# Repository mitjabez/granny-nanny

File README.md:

# About

IoT light sensor app. Light state is sent to a rest endpoint which saves it to Google Cloud
Monitoring.

I use this to monitor the light at my mom's house so I know if she's ok.

The app consists of 2 parts located in `src/`:
- esp8266_monitor. This is the sender built on ESP8266.
- http_iot_streamer. HTTP REST web service storing the data in Google Cloud Monitoring.

# esp8266_monitor

## Prerequisites:

- Copy `config.h.example` to `config.h` and edit all values marked with `CHANGEME`.
- https://github.com/plerup/makeEspArduino

## Build

    make

    make flash

# Hardware

Eagle PCB and schematic files (plus exported PDFs) are in `hardware/`:
- `hardware/granny-nanny.sch` / `hardware/granny-nanny-schematic.pdf` — Schematic
- `hardware/granny-nanny.brd` / `hardware/granny-nanny-board.pdf` — PCB layout

## Known issue: must be powered on in the light

The photocell voltage divider (`R1` + `VR2`) is wired to `GPIO2` on the ESP-01. Because `GPIO2` is a boot-strapping pin that must be `HIGH` at startup, powering on or rebooting the device in the dark (or with the photocell disconnected) allows `VR2` to pull `GPIO2` `LOW`, causing the ESP-01 to hang on boot with both the red and blue LEDs constantly lit.

Make sure there is enough light on the sensor when turning the device on. Once booted, darkness is handled normally.

# http_iot_streamer

## Prerequisites

- Service account named `svc-http-iot-streamer`.
- Copy `.env.yaml.example` to `.env.yaml` and edit the corresponding values. File is located in
`src/http_iot_streamer/`.

## Deploy

    ./scripts/deploy.sh

## Run locally

Create a virtual environment and install the service dependencies:

    cd src/http_iot_streamer
    python3 -m venv .venv
    source .venv/bin/activate
    python -m pip install -r requirements.txt

Set the required configuration values, then start the service:

    export API_KEY=local-api-key
    export ENVIRONMENT=local
    export PROJECT=your-gcp-project-id
    python main.py

The service listens on `http://localhost:8080`. To send it a test request:

    curl --data '{"light": true}' --header 'content-type: application/json' \
      'http://localhost:8080/light/status?apikey=local-api-key'

Valid requests write a metric to Google Cloud Monitoring, so local runs need Google
Cloud credentials that can write metrics to the selected project.

## Test

This will send a test payload to the deployed service:

    ./scripts/test.sh

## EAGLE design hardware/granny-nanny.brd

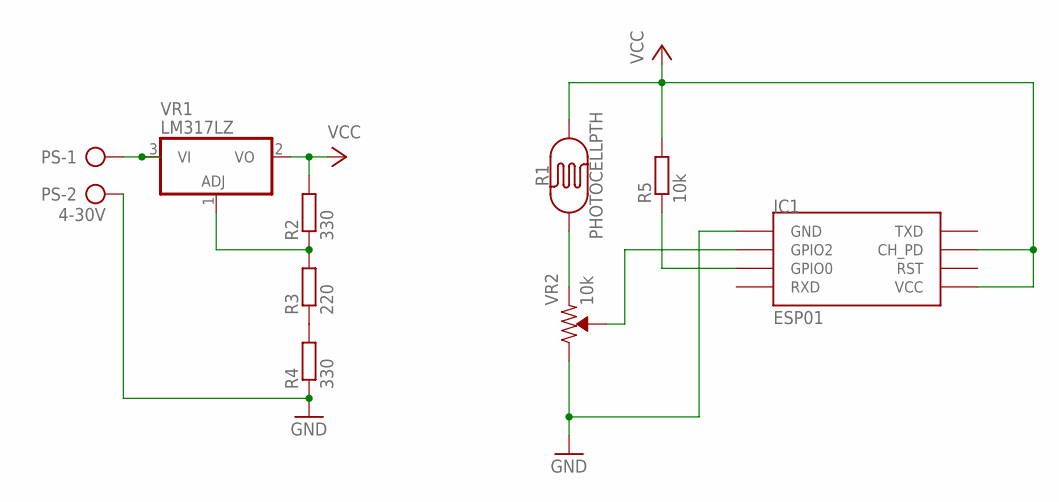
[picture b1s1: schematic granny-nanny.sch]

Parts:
IC1: ESP01
PS: 4-30V; AK500/2
R1: PHOTOCELLPTH; PHOTOCELL
R2, R4: 330; 0207/10
R3: 220; 0207/10
R5: 10k; 0207/10
VR1: LM317LZ; TO92
VR2: 10k; TRIMPOT-PTH-3386U

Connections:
GND: IC1.GND, PS.2, R4.1, VR2.3 (CW)
unnamed: PS.1, VR1.3 (VI)
unnamed: R2.1, R3.2, VR1.1 (ADJ)
unnamed: R3.1, R4.2
unnamed: R1.1, VR2.1 (CCW)
unnamed: IC1.GPIO2, VR2.2 (WIPER)
unnamed: IC1.GPIO0, R5.1
VCC: IC1.CH_PD, IC1.VCC, R1.2, R2.2, R5.2, VR1.2 (VO)

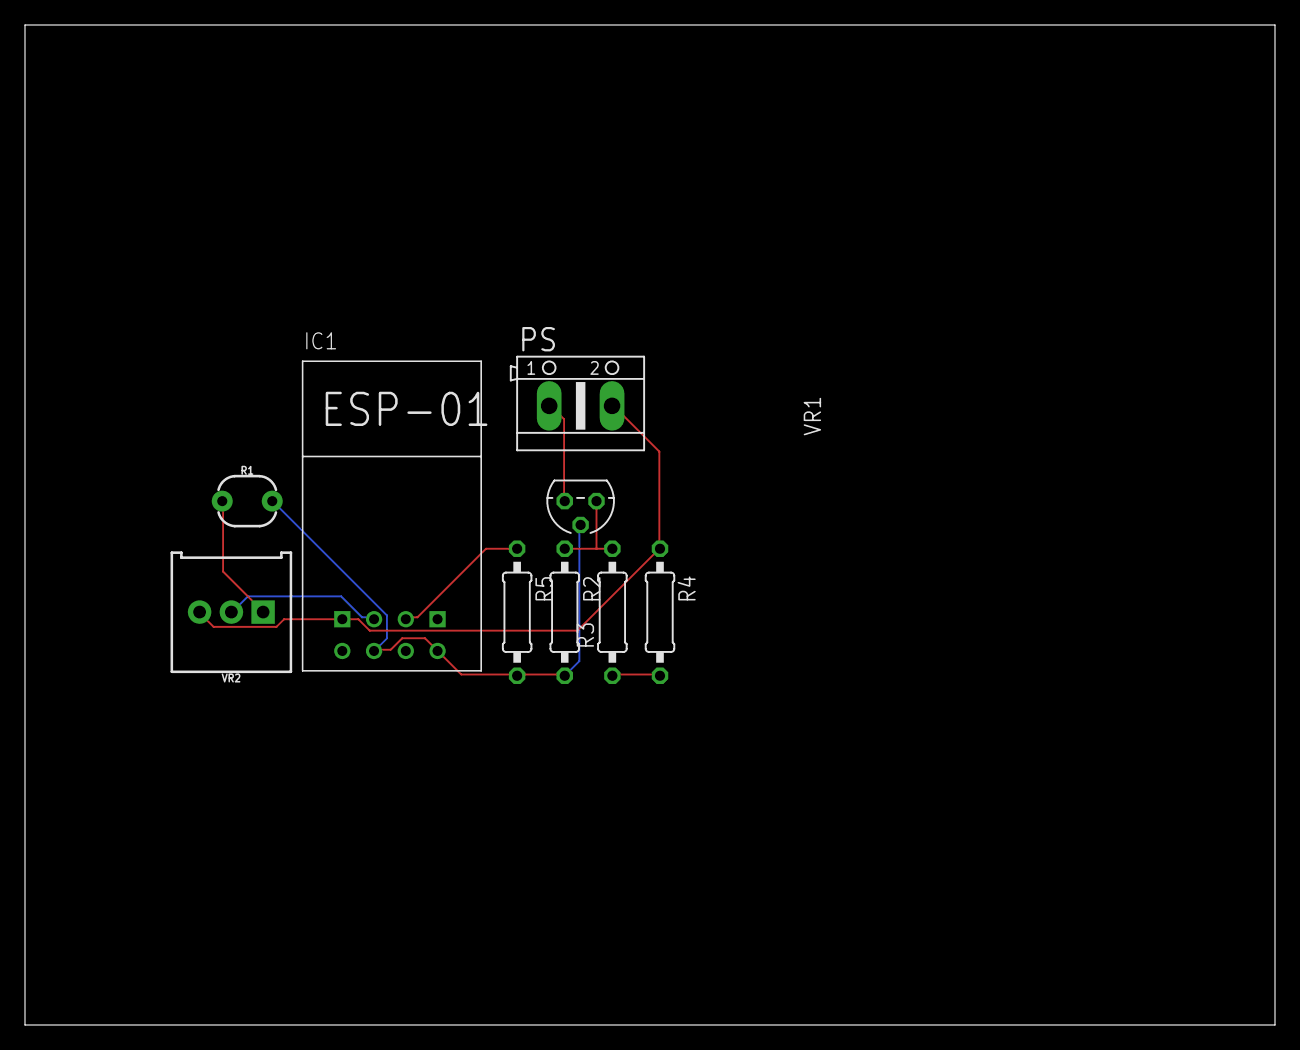
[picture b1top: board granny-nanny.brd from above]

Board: 2 copper layers, 100.0 x 80.0 mm, 9 parts (0 on the bottom side), 8 nets.

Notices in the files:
parts and their libraries:
SparkFun-Sensors: Licensing: Creative Commons ShareAlike 4.0 International - https://creativecommons.org/licenses/by-sa/4.0
